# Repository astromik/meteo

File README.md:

Detaily:<br>
  http://www.astromik.org/raspi/meteo2/

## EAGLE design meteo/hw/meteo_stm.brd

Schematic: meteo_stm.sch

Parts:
AM2302: RHT03_DHT-22_AM2302RA; RHT03_DHT-22/RA
BT1: BT_MODUL
C1, C4: >10uF; CPOL-RADIAL-2.5MM-5MM
C2, C3, C5, C6, C7, C12: 100n; 0805
C8: 220n; 0805
C9: 10u; CPOL-RADIAL-2.5MM-5MM
C10: 33u; CPOL-RADIAL-2.5MM-5MM
C11, C14: 1u; 0805
C13: 220u; C-EL_3,5
C15, C16, C17, C18, C19, C20, C21, C22, C23, C24, C25, C26, C27, C28: ---; 0805
CON1, CON2: MLW10; MLW10G
CON3: MLW06; MLW06G
D1, D2: LED; P1206
EEPROM: 24AA256; SO8
FUSE: 500mA; 1206
IC1: PCF8574T; SO16W
IC2, IC3: MAX481CSA; SO08
IC4: ATTINY85
ISP: PINHD-2X3; 2X03
JP1: PINHD-2X2; 2X02
JP2: PINHD-1X5; 1X05
JP3, JP6: PINHD-1X3; 1X03
JP4, JP5: PINHD-2X5; 2X05
JP7, JP8, JP9, JP10, JP17, JP20: PINHD-1X1; 1X01
K1, K3, K4, K5: ARK500/2
KON-DS18B20: ARK500/3
KON-PWR: ARK500/2
LED1: Modra; LED_3
LED2: Cervena; LED_3
LED3: Zelena; LED_3
LED4: Bila; LED_3
MOD1: MOD_APDS9960
MOD2: MODUL_BMP180
MOD3: MODUL_DS3231; DS3231
P1: 100k; 64Y
PIN1, PIN2: BIGPIN
Q1, Q2: BSS138; SOT23-3
Q3: TP0602N3; TO-92
Q4: BSS295; TO92
R1, R2, R3, R4, R7, R25, R26: 1k; 0805
R5, R6, R23: 4k7; 0805
R8, R9, R10, R11, R12, R13, R14, R18, R19: 10k; 0805
R15, R16, R21, R22: 18k; 0805
R17, R24: 120R; 0805
R20: NEOSAZOVAT; 0805
RAM1, RAM2: 47C16; SO08
REFUSE-PB3: PINHD-1X1; 1X01
REG1: AP1117E33; SOT223
REP1: KPE242
SD1: MICROSD_MODUL
SJ-SCL1: SJ; SJ_2S-NO
SW1: 3-bit; EDG-03
TSOP1: TSOP
U$1: BLUE_PILL

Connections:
0V: BT1.GND, C1.2 (-), C2.1, C3.1, C4.2 (-), C5.1, C24.2, CON1.1, CON3.2, EEPROM.4 (GND), EEPROM.7 (WP), JP2.1, JP5.7, KON-DS18B20.1 (K1), KON-PWR.2 (K2), MOD2.GND, MOD3.GND2, P1.2, Q4.3 (S), RAM1.4 (GND), RAM2.3 (A2), RAM2.4 (GND), SD1.GND, U$1.P$22 (GND)
3.3V: SD1.3,3 (3.3V)
+3V: CON1.8, U$1.P$23 (3.3V)
+5V: C2.2, C3.2, C5.2, CON1.10, CON3.6, EEPROM.1 (A0), EEPROM.2 (A1), EEPROM.3 (A2), EEPROM.8 (VCC), FUSE.1, JP2.5, JP5.5, MOD2.VCC, MOD3.VCC2, Q3.1 (S), R7.1, RAM1.2 (A1), RAM1.3 (A2), RAM1.8 (VCC), RAM2.2 (A1), RAM2.8 (VCC), REP1.+, SD1.VCC, U$1.P$18 (5V)
+PWR: FUSE.2, KON-PWR.1 (K1)
B2_0V: AM2302.GND, C6.1, C7.1, C15.2, C22.2, C24.1, C28.1, CON2.1, IC1.1 (A0), IC1.2 (A1), IC1.3 (A2), IC1.8 (VSS), MOD1.P_GND (GND), SW1.1, SW1.2, SW1.3, TSOP1.GND
B2_+3V: C6.2, CON2.8, IC1.16 (VDD), LED1.A, LED2.A, LED3.A, LED4.A, MOD1.P_VCC (VCC), MOD1.P_VL (VL), Q1.1 (G), Q2.1 (G), R8.1, R10.1
B2_+5V: AM2302.VDD, C7.2, CON2.10, R6.2, R9.1, R11.1, TSOP1.VCC
B2_INFRA: CON2.5, TSOP1.SIGNAL
B2_INT_POHYB: CON2.3, MOD1.P_INT (INT)
B2_LED-BK: IC1.4 (P0), R1.1
B2_LED-GK: IC1.6 (P2), R3.1
B2_LED-RK: IC1.5 (P1), R2.1
B2_LED_I: CON2.9, R4.1
B2_NC3: CON2.6, JP10.1
B2_SCL_H: CON2.4, Q2.3 (D), R11.2
B2_SCL_L: C16.2, C18.2, IC1.14 (SCL), MOD1.P_SCL (SCL), Q2.2 (S), R10.2
B2_SDA_H: CON2.2, Q1.3 (D), R9.2
B2_SDA_L: IC1.15 (SDA), MOD1.P_SDA (SDA), Q1.2 (S), R8.2
B2_VLHKOMER: AM2302.DATA, CON2.7, R6.1
B3_+3V: C10.1 (+), C18.1, C21.1, C22.1, IC2.8 (VCC), R12.2, R13.2, R14.2, REG1.2 (OUT)
B3_+5V: C9.1 (+), C16.1, C17.2, C20.2, C23.2, C25.1, JP4.6, K5.1 (K1), R15.2, REG1.3 (IN)
B3_GND: C9.2 (-), C10.2 (-), C19.2, IC2.5 (GND), JP4.8, K1.2 (K2), R16.1, REG1.1 (GND)
B3_I2C-SCL: JP4.10
B3_I2C-SDA: JP4.4
B3_KOM_A: C15.1, IC2.6 (A), K1.1 (K1), R15.1, R17.1
B3_KOM_B: IC2.7 (B), K5.2 (K2), R16.2, R17.2
B3_NC4: JP4.2
B3_NC6: JP4.3
B3_RS485-RX: IC2.1 (RO), JP4.9, R13.1
B3_RS485-SMER: IC2.2 (RE/), IC2.3 (DE), JP4.5, R14.1
B3_RS485-TX: IC2.4 (DI), JP4.7, R12.1
B3_SPOJKA: JP4.1
B4_+5V: C11.2, C12.2, C13.C+ (C_EL+), C14.2, C19.1, C20.1, C23.1, IC3.8 (VCC), IC4.8 (VCC), ISP.2, JP3.3, JP6.3, K4.1 (K1), R18.2, R19.2, R20.2, R21.2, R23.2
B4_A: IC3.6 (A), K3.1 (K1), R21.1, R24.1
B4_B: IC3.7 (B), K4.2 (K2), R22.2, R24.2
B4_GND: C11.1, C12.1, C13.C- (C_EL-), C14.1, C17.1, C26.1, D1.K, D2.K, IC3.5 (GND), IC4.4 (GND), ISP.6, JP3.1, JP6.1, K3.2 (K2), R22.1
BLUE-RX: BT1.RX, JP1.2
BLUE-TX: BT1.TX, JP1.4
BT-ON: Q3.2 (G), R7.2, U$1.P$27 (PB1)
BT-PWR: BT1.VCC, Q3.3 (D)
BZUK: C8.2, U$1.P$13 (PB5)
BZUK-C: C8.1, P1.1
BZUK-DRAIN: C28.2, Q4.2 (D), REP1.-
BZUK-GATE: P1.3, Q4.1 (G)
DIS-RX: CON3.1, U$1.P$25 (PB11)
DIS-TX: CON3.5, U$1.P$26 (PB10)
DS18B20: KON-DS18B20.2 (K2), R5.2, U$1.P$5 (PA8)
DS18B20-PWR: KON-DS18B20.3 (K3), R5.1, U$1.P$16 (PB8)
GND1: U$1.P$21 (GND1)
I2C-SCL: CON1.4, EEPROM.6 (SCL), JP5.9, MOD2.SCL, MOD3.SCL2, RAM1.6 (SCL), RAM2.6 (SCL), U$1.P$14 (PB6)
I2C-SDA: CON1.2, EEPROM.5 (SDA), JP5.3, MOD2.SDA, MOD3.SDA2, RAM1.5 (SDA), RAM2.5 (SDA), U$1.P$15 (PB7)
INFRA: CON1.5, U$1.P$17 (PB9)
INT_POHYB: C21.2, C27.2, CON1.3, U$1.P$1 (PB12)
INT_RTC: MOD3.SQW, U$1.P$2 (PB13)
KOM-RX: JP1.3, JP2.3, U$1.P$7 (PA10)
KOM-TX: JP1.1, JP2.2, U$1.P$6 (PA9)
LED_I: C25.2, C26.2, CON1.9, U$1.P$3 (PB14)
MISO: SD1.MISO, U$1.P$30 (PA6)
MOSI: SD1.MOSI, U$1.P$29 (PA7)
MOSI-ISP: IC4.5 (MOSI/PB0), ISP.4, R26.1
unnamed: LED1.K, R1.2
unnamed: LED2.K, R2.2
unnamed: LED3.K, R3.2
unnamed: LED4.K, R4.2
unnamed: D2.A, R26.2
unnamed: IC1.11 (P6), SW1.4
unnamed: C4.1 (+), RAM2.1 (VCAP)
unnamed: IC1.10 (P5), SW1.5
unnamed: IC1.9 (P4), SW1.6
unnamed: JP3.2, JP6.2, R23.1, SJ-SCL1.2
unnamed: D1.A, R25.1
unnamed: C1.1 (+), RAM1.1 (VCAP)
NC1: JP7.1, U$1.P$8 (PA11)
NC2: JP8.1, U$1.P$9 (PA12)
NC3: CON1.6, JP9.1, U$1.P$10 (PA15)
NC4: JP5.1, U$1.P$12 (PB4)
NC5: JP17.1, U$1.P$28 (PB0)
NC6: JP5.4, U$1.P$36 (PA0)
RS485-RX: JP5.10, U$1.P$33 (PA3)
RS485-SMER: JP5.6, U$1.P$35 (PA1)
RS485-TX: JP5.8, U$1.P$34 (PA2)
RST-ISP: IC4.1 (RST/PB5), ISP.5
SCK: SD1.SCK, U$1.P$31 (PA5)
SCK-ISP: IC3.2 (RE/), IC3.3 (DE), IC4.7 (SCK/PB2), ISP.3, R20.1, R25.2
SD_CS: SD1.CS, U$1.P$32 (PA4)
SEC-SELC: U$1.P$4 (PB15)
SPOJKA: JP5.2, JP20.1
TINY-PB4: IC3.4 (DI), IC4.3 (PB4), R18.1
TL1: IC3.1 (RO), IC4.2 (PB3), R19.1, REFUSE-PB3.1
VCC2-MISO-ISP: C27.1, IC4.6 (MISO/PB1), ISP.1, SJ-SCL1.1
VLHKOMER: CON1.7, U$1.P$11 (PB3)

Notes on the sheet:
I2C ADDR=0x77
I2C ADDR=0x57
I2C ADDR=0x68
I2C ADDR=0x56
I2C ADDR=0x1E
P-FET
I2C ADDR=0x1A
I2C ADDR=0x52
I2C ADDR=0x39
SEC/SELC
budik_OFF
rezerva
Mechanická podpora rozšiřující desky
konektor pro plochý kabel
dutinky
kolíky
připojení teploměrů DS18B20
(EEPROM odstranit)
V prototypu odzkoušeno s tranzistorem 2N7000, který ale bylo nutno zapájet pootočený.
Místo kondenzátoru pak byla použita propojka.
Převodník napěťových úrovní pro I2C sběrnici
odpojování BT při použití USB převodníku

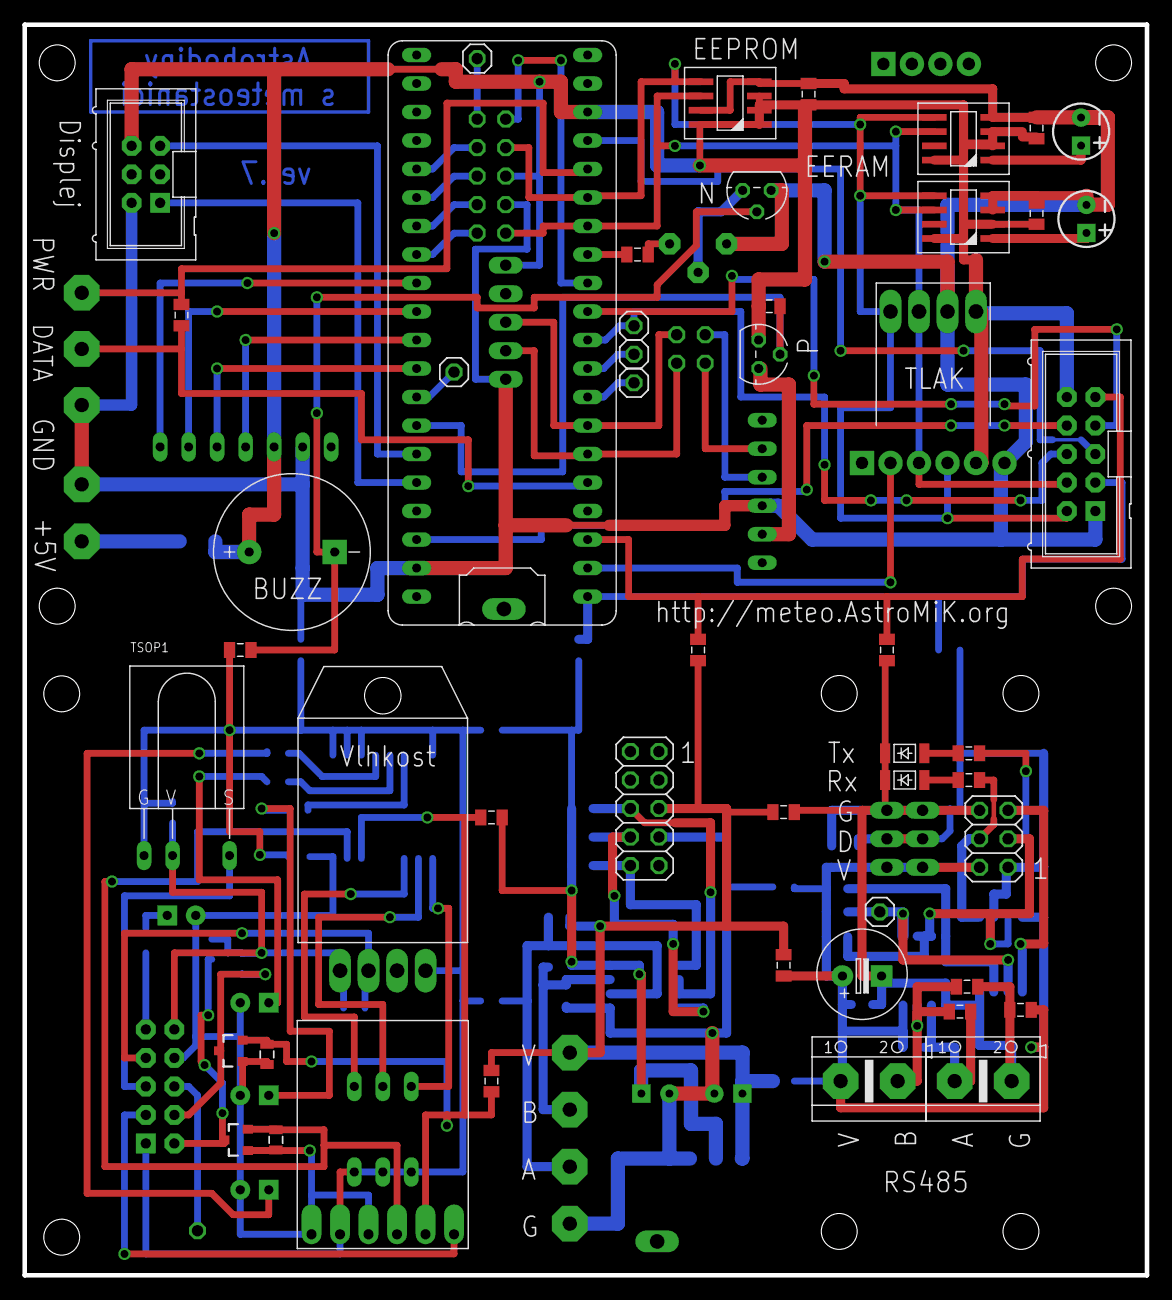
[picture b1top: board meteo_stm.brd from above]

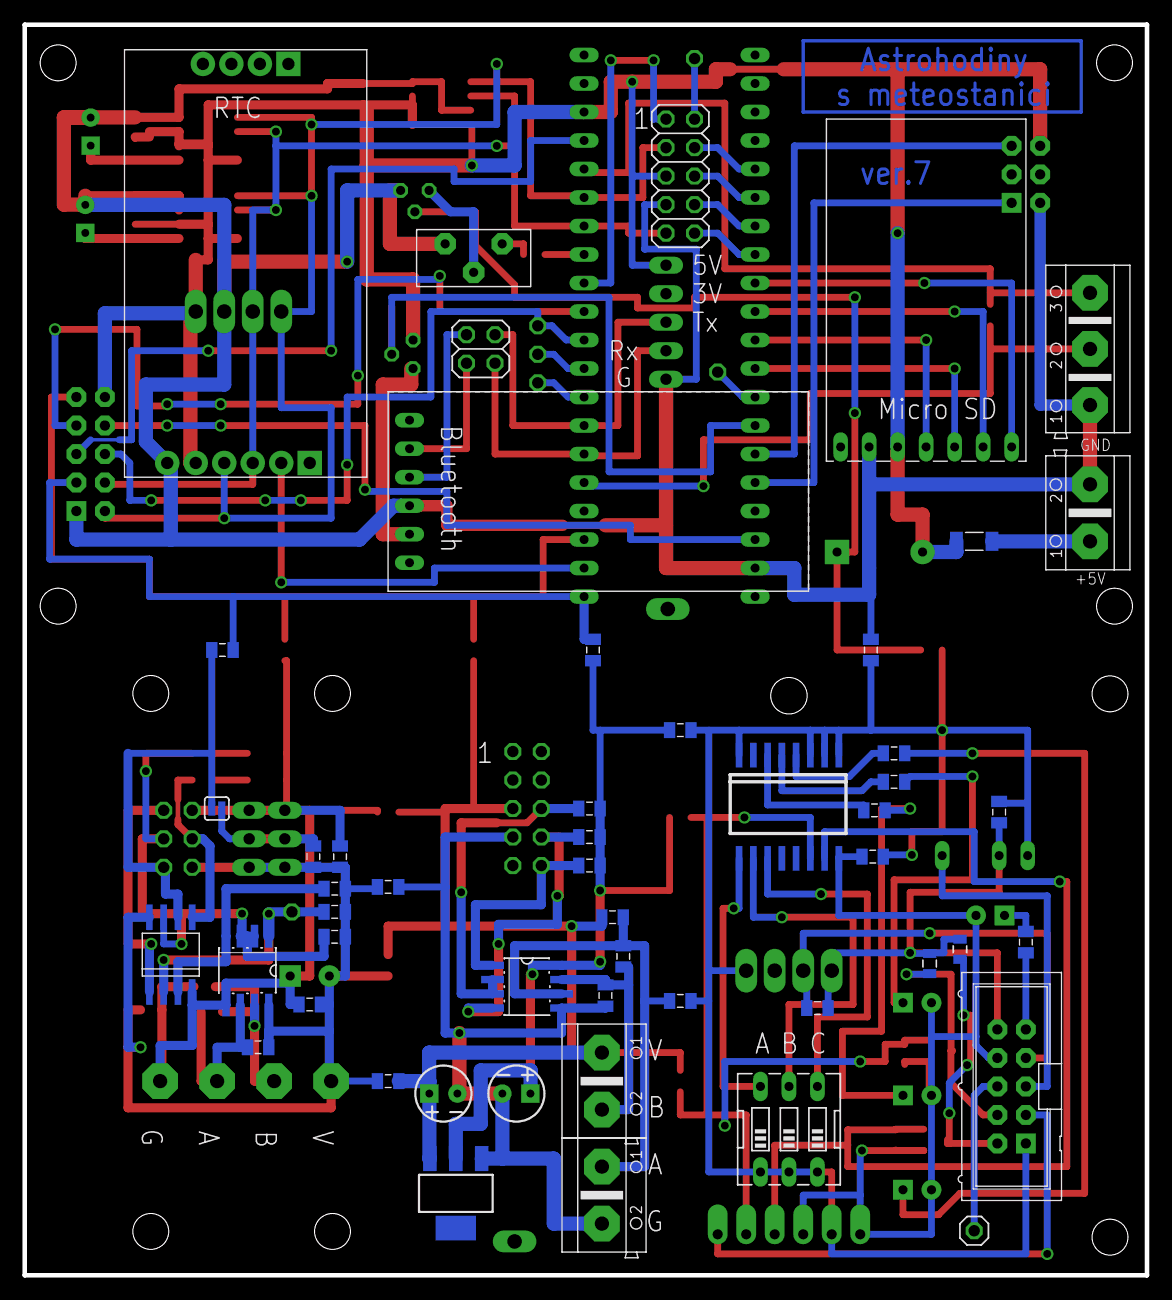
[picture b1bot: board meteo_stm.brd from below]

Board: 2 copper layers, 100.0 x 111.4 mm, 110 parts (52 on the bottom side), 84 nets.

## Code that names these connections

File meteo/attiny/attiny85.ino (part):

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//=============
//                                              ATtiny85
//                                             +--\__/--+
//                          (RESET)    - PB5  1|        |8  Vcc  - napajeni
//       Prevodnik RS485 (pin RO / Rx) - PB3  2|        |7  PB2  - Ovladani smeru komunikace RS485 (piny DE+RE)  
//       Prevodnik RS485 (pin DI / Tx) - PB4  3|        |6  PB1  - teplomery DS18B20
//                                       GND  4|        |5  PB0  - signalizacni LED
//                                             +--------+
//
//
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#define pin_TX         4                   // RS485 (DI)
#define pin_RX         3                   // RS485 (RO)
#define pin_DE_RE      2                   // RS485 - (DE,RE) - prepinani smeru komunikace
#define ONE_WIRE_BUS   1                   // Pin pro teplomery DS18B20
#define pin_LED        0                   // Pin pro informacni LED


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
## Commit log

2019-09-15 Add files via upload
    První zveřejněná verze
2019-09-15 Add files via upload
    Oprava problému s rozsvěcováním displeje v minutě, ve které končí budík.
    (Když budík skončil a displej zhasnul, musela se provést dvojitá aktivace čidla přiblížení, aby se displej opět rozsvítil.)

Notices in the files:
parts and their libraries:
SparkFun-Capacitors: Licensing: Creative Commons ShareAlike 4.0 International - https://creativecommons.org/licenses/by-sa/4.0
Copyright (C) PaJa 2011
Copyright (C) PaJa 2001-2011
